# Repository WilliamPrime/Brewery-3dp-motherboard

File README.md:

# Brewery-3dp-motherboard
A 3d printer expansion board designed to help with monitoring and managing thermals in a 3d printer

# Key featurs

- supports 12-30V input
-20 buffered thermistor inputs
- 12 fan outputs each with selection between 5V,12V and Vbus
- 12V is dropped down with a buck converter on the board with 12A max
  - if the input voltage is 12V the 12V buck shouldnt be used
- 5V is dropped down with a buck converter on the board with 12A max

- 4 Pwmed outputs meant for heaters or really beefy fans
- 35A max per output, 62A max across all of the ports
  - the heaters are on a seperate fuse and terminal in, allowing you to save power budget for fans or just run things at a different voltage.

So you could you could use the thermistors to do something like 

- 12 for motors
  - would allow for checking in places where you suspect hotspots, but also coldspots.
  - would montior, Extruder, Z, and then 4 motor for an AWD gantry
- temp of outside of pannels
- ambient air temp
- electronics enclosure air temp
- lower printer air temp
- mid printer air temp
- upper printer air temp
- bed edge temp 
- frame temp

# KiCAD photos

# Firmware

This board uses an STM32F407ZGT6 MCU, which is supported by mainline klipper and marlin.

# BOM

| Part              | Item cost | shipping+tax cost | Total cost for item(s) | Notes                                 |
|-------------------|-----------|-------------------|------------------------|---------------------------------------|
| LCSC components   | $157.72   | $39.63            | $190.90                | ordering enough to populate the 5PCBs |
| JLC PCB + stencil | $92.09    | $48.06            | $140.15                | No PCBA, im handsoldering, the boards |
|                   |           |                   |                        |                                       |

Total cost $331.05

There is a detailed break down of the parts to be ordered on LCSC [**here**](https://github.com/WilliamPrime/Brewery-3dp-motherboard/blob/main/PROD/Brewery_Alpha_0.01_LCSC%20bom.csv)

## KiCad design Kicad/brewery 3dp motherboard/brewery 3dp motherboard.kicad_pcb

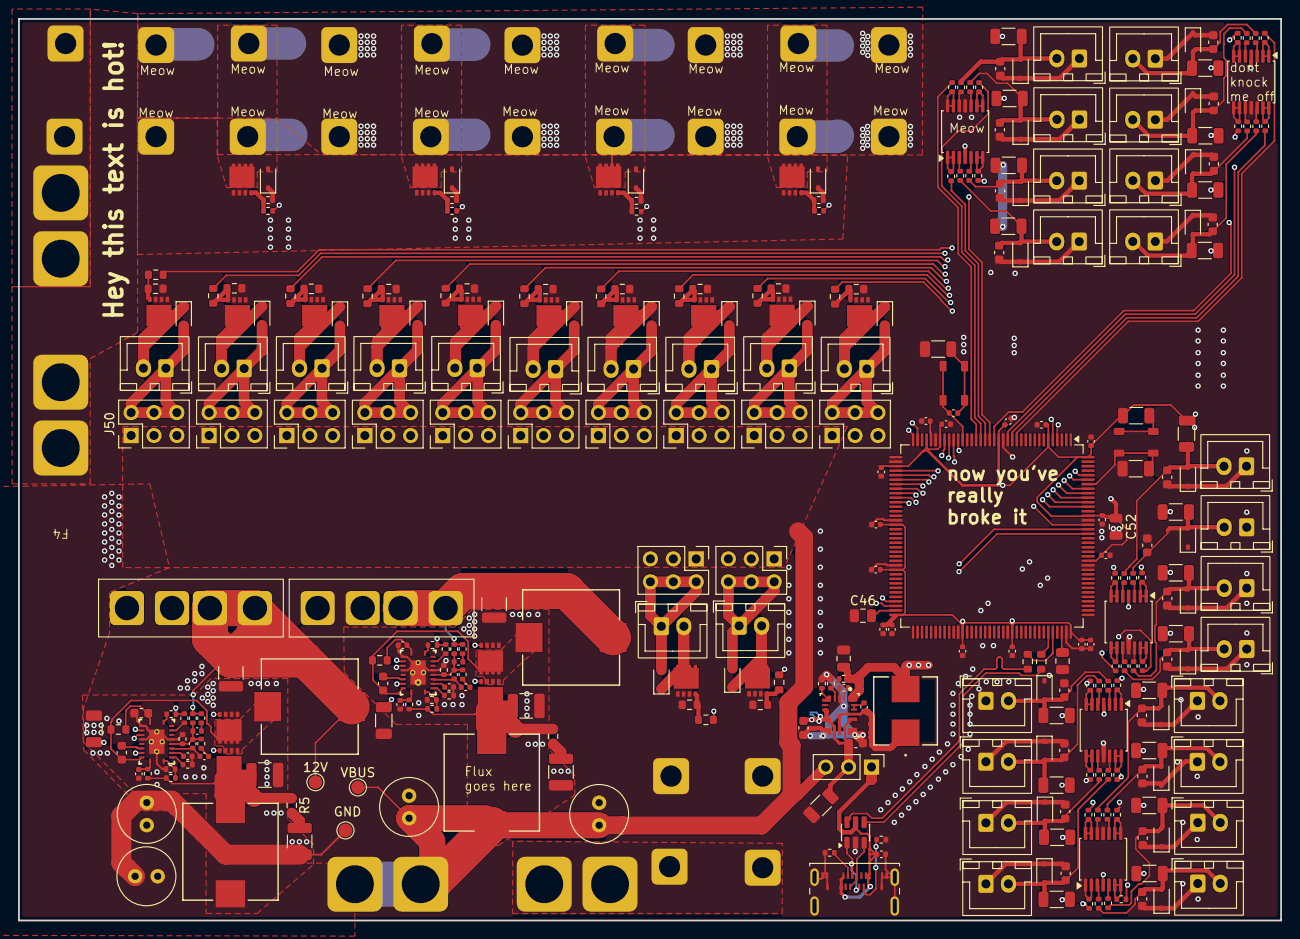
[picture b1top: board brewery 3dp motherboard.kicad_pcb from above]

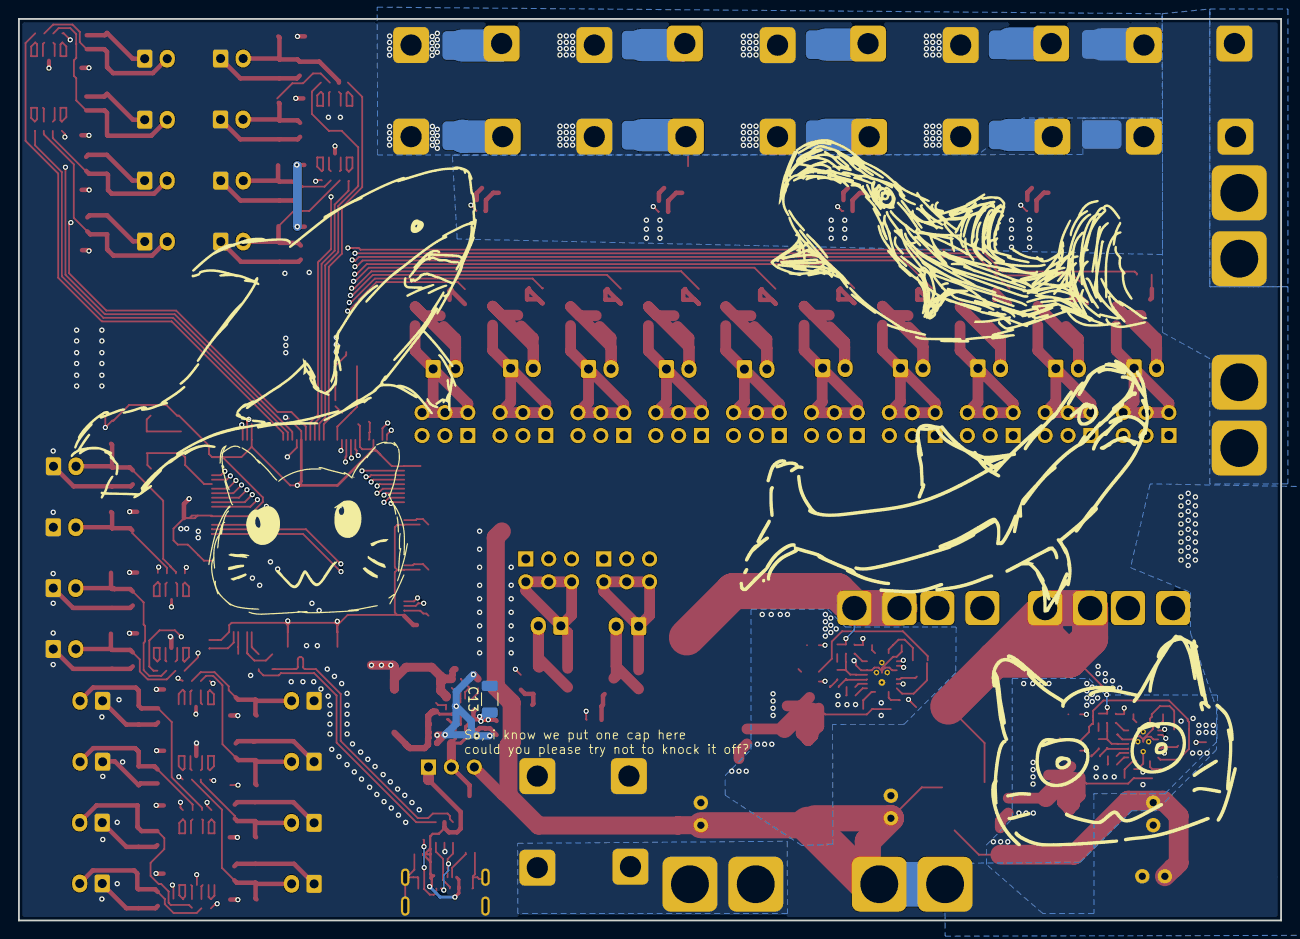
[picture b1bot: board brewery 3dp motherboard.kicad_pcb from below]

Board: 4 copper layers, 140.0 x 100.0 mm, 337 parts (6 on the bottom side), 208 nets.

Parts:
12V: TestPoint_Pad_D1.5mm
C2, C4, C22, C23: 47uF; C_Radial_D6.3mm_H7.0mm_P2.50mm
C3, C6, C7, C8, C9, C10, C72, C73, C74, C75, C76, C77, C78, C79, C80, C81, C82, C83, C84, C85, C86, C87: 4.7uF; C_0603_1608Metric
C5, C24: 10uF; C_1210_3225Metric
C11, C12: 4.7uF; C_1210_3225Metric
C13, C14: 470nF; C_1206_3216Metric
C15, C16, C26, C39, C44, C53, C54, C55, C56, C57, C58, C59, C60, C61, C66, C67, C68, C69, C70, C71: 100nF; C_0402_1005Metric
C17, C45: 1uF; C_0402_1005Metric
C18, C19: 56nF; C_0402_1005Metric
C20, C21: 2.2uF; C_1206_3216Metric
C27, C28: 100nF; C_0603_1608Metric
C29: 6.8pF; C_0603_1608Metric
C30: 6.8pF; C_0402_1005Metric
C31, C32: 8.2nF; C_0402_1005Metric
C33, C34: 1nF; C_0402_1005Metric
C35: 47uF; C_0805_2012Metric
C40, C41: 390pF; C_0402_1005Metric
C42, C43: 22uF; C_1210_3225Metric
C46, C47: 2.2uF; C_0805_2012Metric
C52: 4.7uF; C_0805_2012Metric
D1, D2, D3, D4, D21, D22, D23, D24, D25, D26, D27, D28, D29, D30, D31, D32, D33, D34, D35, D36, D37, D38, D39, D40, D41, D42, D43, D44, D45, D46, D47, D48, D49, D50, D51, D52: D55V0M1B2WS-7; D_SOD-323
F1, F4: Fuse; Untitled
F2, F3: Fuse; XF-509P
GND: TestPoint_Pad_D1.5mm
J1: power in; KF135T-10.16-2P
J2, J3, J4, J5, J29, J31, J33, J35, J37, J39, J41, J43, J45, J47, J49, J51, J52, J53, J54, J55, J56, J57, J58, J59, J60, J61, J62, J63, J64, J65, J66, J67: JST-XH; JST_XH_B2B-XH-A_1x02_P2.50mm_Vertical
J6: Conn_01x03_Pin; PinHeader_1x03_P2.54mm_Vertical
J11: USB_C_Receptacle_USB2.0_14P; USB_C_Receptacle_Amphenol_124019772112A
J16: heater in; KF135T-10.16-2P
J26, J27, J68, J69: Screw_Terminal_01x02; KF135T-10.16-2P
J28, J30, J32, J34, J36, J38, J40, J42, J44, J46, J48, J50: jumpers; PinHeader_2x03_P2.54mm_Vertical
L1, L2, L4, L5: 3.3uH; IND_SRP1038A_BRN-M
L3: 2.2uH; 7x6.6mm-inductor-M
R1, R2, R3, R4, R29, R122, R123, R128, R129, R134, R135, R140, R141, R146, R147, R152, R153, R158, R159, R164, R165: 4.7k; R_1206_3216Metric
R5, R6: 1ohm; R_0603_1608Metric
R7, R8, R9, R10, R15, R16, R17, R18, R124, R125, R126, R127, R130, R131, R132, R133, R136, R137, R138, R139, R142, R143, R144, R145, R148, R149, R150, R151, R154, R155, R156, R157, R160, R161, R162, R163, R166, R167, R168, R169: 1k; R_0402_1005Metric
R11, R13: 80.4k; R_0402_1005Metric
R12, R14: 8.45k; R_0402_1005Metric
R19, R20: 2.1ohm; R_0402_1005Metric
R21: 5.76k; R_0402_1005Metric
R22, R23, R24, R25, R26, R27: 20k; R_0402_1005Metric
R28, R30: 100; R_1206_3216Metric
R40: 51k; R_0402_1005Metric
R41: 22.1K; R_0402_1005Metric
R42, R43: 1.02k; R_0603_1608Metric
R44, R45: 1.47k; R_0402_1005Metric
R46: 1.5k; R_0402_1005Metric
R47: 3.4k; R_0402_1005Metric
R52, R53: 5.1k; R_0402_1005Metric
R54: 21k; R_0402_1005Metric
R55: 18k; R_0402_1005Metric
R60, R61: 130ohm; R_0402_1005Metric
R80, R84, R86, R88: 100; R_0402_1005Metric
R81, R85, R87, R89: 10k; R_0402_1005Metric
R82, R83: 22; R_0603_1608Metric
R90, R91, R92, R93, R94: 0Ohm; Milliohm HoT-2-4.5-11-I
R98, R100, R102, R104, R106, R108, R110, R112, R114, R116, R118, R120: 2k; R_0603_1608Metric
R99, R101, R103, R105, R107, R109, R111, R113, R115, R117, R119, R121: 20k; R_0603_1608Metric
SW1, SW2: SW_Push; CAX TS-1185-W-4P-H1.8-160
U1, U30, U31, U32, U33: MCP6004; TSSOP-14_4.4x5mm_P0.65mm
U2: LM61430AFSQRJRRQ1; RJR0014A-MFG
U4, U5: LM25145RGYR; RGY0020B
U7, U8, U9, U10, U16, U17, U18, U19, U20, U21, U22, U23, U24, U25, U26, U27, U28, U29, U34, U35: DOZ45N03T
U11: USBLC6-2SC6; SOT-23-6
U14: STM32F407Z_E-G_Tx; LQFP-144_20x20mm_P0.5mm
VBUS: TestPoint_Pad_D1.5mm

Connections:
+3.3V: C35.1, C52.1, C53.1, C54.1, C55.1, C56.1, C57.1, C58.1, C59.1, C60.1, C61.1, C66.1, C67.1, C68.1, C69.1, C70.1, C71.1, L3.2, R1.2, R2.2, R3.2, R4.2, R28.1, R40.2, R122.2, R123.2, R128.2, R129.2, R134.2, R135.2, R140.2, R141.2, R146.2, R147.2, R152.2, R153.2, R158.2, R159.2, R164.2, R165.2, U1.4 (V+), U2.1 (BIAS), U14.6 (VBAT), U14.17 (VDD), U14.30 (VDD), U14.33 (VDDA), U14.39 (VDD), U14.52 (VDD), U14.62 (VDD), U14.72 (VDD), U14.84 (VDD), U14.95 (VDD), U14.108 (VDD), U14.121 (VDD), U14.131 (VDD), U14.144 (VDD), U30.4 (V+), U31.4 (V+), U32.4 (V+), U33.4 (V+)
+5V: F3.1, J28.5, J30.5, J32.5, J34.5, J36.5, J38.5, J40.5, J42.5, J44.5, J46.5, J48.5, J50.5
+12V: F2.1, J28.3, J30.3, J32.3, J34.3, J36.3, J38.3, J40.3, J42.3, J44.3, J46.3, J48.3, J50.3
BOOT0: R29.2, SW2.2, U14.138 (BOOT0)
Fan1: R98.1, U14.127 (PG12)
Fan2: R106.1, U14.128 (PG13)
Fan3: R100.1, U14.129 (PG14)
Fan4: R108.1, U14.133 (PB3)
Fan5: R102.1, U14.134 (PB4)
Fan6: R110.1, U14.135 (PB5)
Fan7: R104.1, U14.136 (PB6)
Fan8: R112.1, U14.137 (PB7)
Fan9: R114.1, U14.139 (PB8)
Fan10: R118.1, U14.140 (PB9)
Fan11: R116.1, U14.5 (PE6)
Fan12: R120.1, U14.4 (PE5)
GND: C2.2, C3.2, C4.2, C5.2, C6.2, C7.2, C8.2, C9.2, C10.2, C11.2, C12.2, C13.2, C14.2, C15.2, C16.2, C17.2, C18.2, C19.2, C20.2, C21.2, C22.2, C23.2, C24.2, C29.2, C30.2, C35.2, C39.1, C42.2, C43.2, C45.1, C46.1, C47.1, C52.2, C53.2, C54.2, C55.2, C56.2, C57.2, C58.2, C59.2, C60.2, C61.2, C66.2, C67.2, C68.2, C69.2, C70.2, C71.2, C72.2, C73.2, C74.2, C75.2, C76.2, C77.2, C78.2, C79.2, C80.2, C81.2, C82.2, C83.2, C84.2, C85.2, C86.2, C87.2, D1.1 (A1), D2.1 (A1), D3.1 (A1), D4.1 (A1), D33.1 (A1), D34.1 (A1), D35.1 (A1), D36.1 (A1), D37.1 (A1), D38.1 (A1), D39.1 (A1), D40.1 (A1), D41.1 (A1), D42.1 (A1), D43.1 (A1), D44.1 (A1), D45.1 (A1), D46.1 (A1), D47.1 (A1), D48.1 (A1), D49.1 (A1), D50.1 (A1), D51.1 (A1), D52.1 (A1), GND.1, J1.1, J2.1, J3.1, J4.1, J5.1, J11.A1 (GND), J11.A12 (GND), J11.B1 (GND), J11.B12 (GND), J11.SH (SHIELD), J16.1, J52.1, J53.1, J54.1, J55.1, J56.1, J57.1, J58.1, J59.1, J60.1, J61.1, J62.1, J63.1, J64.1, J65.1, J66.1, J67.1, R12.1, R14.1, R21.2, R22.1, R23.1, R29.1, R30.1, R41.1, R46.1, R47.1, R52.2, R53.2, R81.1, R85.1, R87.1, R89.1, R94.1, R94.2, R99.1, R101.1, R103.1, R105.1, R107.1, R109.1, R111.1, R113.1, R115.1, R117.1, R119.1, R121.1, U1.11 (V-), U2.3 (AGND), U2.9 (PGND1), U2.11 (PGND2), U4.6 (AGND), U4.12 (PGND), U4.15 (EP), U4.21 (EP), U4.GND, U5.6 (AGND), U5.12 (PGND), U5.15 (EP), U5.21 (EP), U5.GND, U8.1 (Source), U10.1 (Source), U11.2 (GND), U14.16 (VSS), U14.31 (VSSA), U14.38 (VSS), U14.51 (VSS), U14.61 (VSS), U14.83 (VSS), U14.94 (VSS), U14.107 (VSS), U14.120 (VSS), U14.130 (VSS), U16.1 (Source), U17.1 (Source), U18.1 (Source), U19.1 (Source), U20.1 (Source), U21.1 (Source), U22.1 (Source), U23.1 (Source), U24.1 (Source), U25.1 (Source), U26.1 (Source), U27.1 (Source), U28.1 (Source), U29.1 (Source), U30.11 (V-), U31.11 (V-), U32.11 (V-), U33.11 (V-), U34.1 (Source), U35.1 (Source)
Heater1: R84.1, U14.70 (PB11)
Heater2: R86.1, U14.69 (PB10)
Heater3: R80.1, U14.36 (PA2)
Heater4: R88.1, U14.35 (PA1)
unnamed: C5.1, R6.1
unnamed: C24.1, R5.2
unnamed: C31.2, R44.2
unnamed: C32.2, R45.2
unnamed: C40.1, R60.1
unnamed: C41.1, R61.1
unnamed: 12V.1, C42.1, F2.2, L4.2, R54.2, R60.2
unnamed: C43.1, F3.2, L5.2, R55.2, R61.2
unnamed: C44.1, R30.2, SW1.1
unnamed: C6.1, D1.2 (A2), J2.2, R1.1, R7.2
unnamed: C7.1, D2.2 (A2), J3.2, R2.1, R8.2
unnamed: C8.1, D3.2 (A2), J4.2, R3.1, R9.2
unnamed: C9.1, D4.2 (A2), J5.2, R4.1, R10.2
unnamed: D21.1 (A1), J29.2, U18.3 (Drain)
unnamed: D21.2 (A2), J28.2, J28.4, J28.6, J29.1
unnamed: D22.1 (A1), J31.2, U19.3 (Drain)
unnamed: D22.2 (A2), J30.2, J30.4, J30.6, J31.1
unnamed: D23.1 (A1), J33.2, U20.3 (Drain)
unnamed: D23.2 (A2), J32.2, J32.4, J32.6, J33.1
unnamed: D24.1 (A1), J35.2, U21.3 (Drain)
unnamed: D24.2 (A2), J34.2, J34.4, J34.6, J35.1
unnamed: D25.1 (A1), J37.2, U22.3 (Drain)
unnamed: D25.2 (A2), J36.2, J36.4, J36.6, J37.1
unnamed: D26.1 (A1), J39.2, U23.3 (Drain)
unnamed: D26.2 (A2), J38.2, J38.4, J38.6, J39.1
unnamed: D27.1 (A1), J41.2, U24.3 (Drain)
unnamed: D27.2 (A2), J40.2, J40.4, J40.6, J41.1
unnamed: D28.1 (A1), J43.2, U25.3 (Drain)
unnamed: D28.2 (A2), J42.2, J42.4, J42.6, J43.1
unnamed: D29.1 (A1), J45.2, U26.3 (Drain)
unnamed: D29.2 (A2), J44.2, J44.4, J44.6, J45.1
unnamed: D30.1 (A1), J47.2, U27.3 (Drain)
unnamed: D30.2 (A2), J46.2, J46.4, J46.6, J47.1
unnamed: D31.1 (A1), J49.2, U28.3 (Drain)
unnamed: D31.2 (A2), J48.2, J48.4, J48.6, J49.1
unnamed: D32.1 (A1), J51.2, U29.3 (Drain)
unnamed: D32.2 (A2), J50.2, J50.4, J50.6, J51.1
unnamed: C72.1, D33.2 (A2), J52.2, R122.1, R124.2
unnamed: C73.1, D34.2 (A2), J53.2, R123.1, R125.2
unnamed: C74.1, D35.2 (A2), J54.2, R128.1, R130.2
unnamed: C75.1, D36.2 (A2), J55.2, R129.1, R131.2
unnamed: C76.1, D37.2 (A2), J56.2, R134.1, R136.2
unnamed: C77.1, D38.2 (A2), J57.2, R135.1, R137.2
unnamed: C78.1, D39.2 (A2), J58.2, R140.1, R142.2
unnamed: C79.1, D40.2 (A2), J59.2, R141.1, R143.2
unnamed: C80.1, D41.2 (A2), J60.2, R146.1, R148.2
unnamed: C81.1, D42.2 (A2), J61.2, R147.1, R149.2
unnamed: C82.1, D43.2 (A2), J62.2, R152.1, R154.2
unnamed: C83.1, D44.2 (A2), J63.2, R153.1, R155.2
unnamed: C84.1, D45.2 (A2), J64.2, R158.1, R160.2
unnamed: C85.1, D46.2 (A2), J65.2, R159.1, R161.2
unnamed: C86.1, D47.2 (A2), J66.2, R164.1, R166.2
unnamed: C87.1, D48.2 (A2), J67.2, R165.1, R167.2
unnamed: D49.2 (A2), J26.2, R90.1, R90.2, U16.3 (Drain)
unnamed: D50.2 (A2), J68.2, R91.1, R91.2, U34.3 (Drain)
unnamed: D51.2 (A2), J69.2, R92.1, R92.2, U35.3 (Drain)
unnamed: D52.2 (A2), J27.2, R93.1, R93.2, U17.3 (Drain)
unnamed: F1.2, J1.2
unnamed: C3.1, C10.1, C13.1, C14.1, J6.2, U2.7 (EN_SYNC), U2.8 (VIN1), U2.12 (VIN2)
unnamed: J11.A5 (CC1), R52.1
unnamed: J11.B5 (CC2), R53.1
unnamed: J11.A6 (D+), J11.B6 (D+), U11.1 (I/O1)
unnamed: J11.A7 (D-), J11.B7 (D-), U11.3 (I/O2)
unnamed: F4.2, J16.2
unnamed: R28.2, SW2.1
unnamed: R7.1, U1.3 (+)
unnamed: R15.2, U1.1, U1.2 (-)
unnamed: R8.1, U1.5 (+)
unnamed: R16.2, U1.6 (-), U1.7
unnamed: R10.1, U1.10 (+)
unnamed: R18.2, U1.8, U1.9 (-)
unnamed: R9.1, U1.12 (+)
unnamed: R17.2, U1.13 (-), U1.14
unnamed: C26.1, U2.13 (RBOOT), U2.14 (CBOOT)
unnamed: R40.1, R41.2, U2.4 (FB)
unnamed: R21.1, U2.5 (PGOOD)
unnamed: C26.2, L3.1, U2.10 (SW)
unnamed: C17.1, U2.2 (VCC)
unnamed: C27.1, U4.17 (BST)
unnamed: C31.1, C33.1, U4.4 (COMP)
unnamed: R11.1, R12.2, U4.1 (EN_UVLO)
unnamed: C33.2, C40.2, R44.1, R46.2, R54.1, U4.5 (FB)
unnamed: U4.18 (HO), U7.2 (Gate)
unnamed: C29.1, R42.2, U4.11 (ILIM)
unnamed: U4.13 (LO), U8.2 (Gate)
unnamed: R25.1, U4.10 (PGOOD)
unnamed: R22.2, U4.2 (RT)
unnamed: C18.1, U4.3 (SS_TRK)
unnamed: C27.2, L4.1, R42.1, U4.19 (SW), U7.1 (Source), U8.3 (Drain)
unnamed: R24.1, U4.8 (SYNCIN)
unnamed: C20.1, R24.2, R25.2, U4.14 (VCC)
unnamed: C15.1, R19.1, U4.20 (VIN)
unnamed: C28.1, U5.17 (BST)
unnamed: C32.1, C34.1, U5.4 (COMP)
unnamed: R13.1, R14.2, U5.1 (EN_UVLO)
unnamed: C34.2, C41.2, R45.1, R47.2, R55.1, U5.5 (FB)
unnamed: U5.18 (HO), U9.2 (Gate)
unnamed: C30.1, R43.2, U5.11 (ILIM)
unnamed: R27.1, U5.10 (PGOOD)
unnamed: R23.2, U5.2 (RT)
unnamed: C19.1, U5.3 (SS_TRK)
unnamed: R26.1, U5.8 (SYNCIN)
unnamed: C21.1, R26.2, R27.2, U5.14 (VCC)
unnamed: C16.1, R20.1, U5.20 (VIN)
unnamed: C11.1, L1.2, R5.1, R11.2, R19.2, U7.3 (Drain)
unnamed: C12.1, L2.2, R6.2, R13.2, R20.2, U9.3 (Drain)
unnamed: C28.2, L5.1, R43.1, U5.19 (SW), U9.1 (Source), U10.3 (Drain)
unnamed: U5.13 (LO), U10.2 (Gate)
unnamed: C44.2, SW1.2, U14.25 (NRST)
unnamed: R82.1, U14.103 (PA11)
unnamed: R83.1, U14.104 (PA12)
unnamed: C46.2, U14.71 (VCAP_1)
unnamed: C47.2, U14.106 (VCAP_2)
unnamed: C45.2, U14.32 (VREF+)
unnamed: R80.2, R81.2, U16.2 (Gate)
unnamed: R88.2, R89.2, U17.2 (Gate)
unnamed: R98.2, R99.2, U18.2 (Gate)
unnamed: R100.2, R101.2, U19.2 (Gate)
unnamed: R102.2, R103.2, U20.2 (Gate)
unnamed: R104.2, R105.2, U21.2 (Gate)
unnamed: R106.2, R107.2, U22.2 (Gate)
unnamed: R108.2, R109.2, U23.2 (Gate)
unnamed: R110.2, R111.2, U24.2 (Gate)
unnamed: R112.2, R113.2, U25.2 (Gate)
unnamed: R114.2, R115.2, U26.2 (Gate)
unnamed: R116.2, R117.2, U27.2 (Gate)
unnamed: R118.2, R119.2, U28.2 (Gate)
unnamed: R120.2, R121.2, U29.2 (Gate)
unnamed: R124.1, U30.3 (+)
unnamed: R126.2, U30.1, U30.2 (-)
unnamed: R125.1, U30.5 (+)
unnamed: R127.2, U30.6 (-), U30.7
unnamed: R131.1, U30.10 (+)
unnamed: R133.2, U30.8, U30.9 (-)
unnamed: R130.1, U30.12 (+)
unnamed: R132.2, U30.13 (-), U30.14
unnamed: R136.1, U31.3 (+)
unnamed: R138.2, U31.1, U31.2 (-)
unnamed: R137.1, U31.5 (+)
unnamed: R139.2, U31.6 (-), U31.7
unnamed: R143.1, U31.10 (+)
unnamed: R145.2, U31.8, U31.9 (-)
unnamed: R142.1, U31.12 (+)
unnamed: R144.2, U31.13 (-), U31.14
unnamed: R148.1, U32.3 (+)
unnamed: R150.2, U32.1, U32.2 (-)
unnamed: R149.1, U32.5 (+)
unnamed: R151.2, U32.6 (-), U32.7
unnamed: R155.1, U32.10 (+)
unnamed: R157.2, U32.8, U32.9 (-)
unnamed: R154.1, U32.12 (+)
unnamed: R156.2, U32.13 (-), U32.14
unnamed: R160.1, U33.3 (+)
unnamed: R162.2, U33.1, U33.2 (-)
unnamed: R161.1, U33.5 (+)
unnamed: R163.2, U33.6 (-), U33.7
unnamed: R167.1, U33.10 (+)
unnamed: R169.2, U33.8, U33.9 (-)
unnamed: R166.1, U33.12 (+)
unnamed: R168.2, U33.13 (-), U33.14
unnamed: R84.2, R85.2, U34.2 (Gate)
unnamed: R86.2, R87.2, U35.2 (Gate)
Thermistor1: R15.1, U14.40 (PA4)
Thermistor2: R16.1, U14.45 (PC5)
Thermistor3: R17.1, U14.41 (PA5)
Thermistor4: R18.1, U14.46 (PB0)
Thermistor5: R126.1, U14.47 (PB1)
Thermistor6: R127.1, U14.43 (PA7)
Thermistor7: R132.1, U14.44 (PC4)
Thermistor8: R133.1, U14.42 (PA6)
Thermistor9: R138.1, U14.26 (PC0)
Thermistor10: R139.1, U14.27 (PC1)
Thermistor11: R144.1, U14.28 (PC2)
Thermistor12: R145.1, U14.29 (PC3)
Thermistor13: R150.1, U14.13 (PF3)
Thermistor14: R151.1, U14.18 (PF6)
Thermistor15: R156.1, U14.14 (PF4)
Thermistor16: R157.1, U14.15 (PF5)
Thermistor17: R162.1, U14.20 (PF8)
Thermistor18: R163.1, U14.19 (PF7)
Thermistor19: R168.1, U14.22 (PF10)
Thermistor20: R169.1, U14.21 (PF9)
USB5V: C39.2, J6.1, J11.A4 (VBUS), J11.A9 (VBUS), J11.B4 (VBUS), J11.B9 (VBUS), U11.5 (VBUS)
USB_D+: R83.2, U11.6 (I/O1)
USB_D-: R82.2, U11.4 (I/O2)
VBUS: C2.1, C4.1, C22.1, C23.1, F1.1, J6.3, J28.1, J30.1, J32.1, J34.1, J36.1, J38.1, J40.1, J42.1, J44.1, J46.1, J48.1, J50.1, L1.1, L2.1, VBUS.1
VHeaters: F4.1, J26.1, J27.1, J68.1, J69.1

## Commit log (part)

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2026-06-07 Initialize README with project details
    Added project description for Brewery-3dp-motherboard.
2026-06-07 Add initial project journal for Klipper board modification
    Document initial project setup and requirements for modifying a Klipper board, including MCU selection and thermistor input specifications.
2026-06-08 Corrected myself
2026-06-11 Update journal with fan circuit design progress
    Documented progress on fan circuit design, including overcurrent protection decisions, MOSFET selection, and thermistor integration. Updated task list and overall schematic.
2026-06-17 did some stuff
2026-06-20 did stuff
2026-06-22 did more stuff
2026-06-22 did stuff (uploading kicad bits)
2026-06-25 Update journal with BOM component selection details
    Documented the process of selecting components for the BOM, including considerations for voltage ratings and component availability.
2026-06-25 Enhance README with features and specifications
    Added detailed features and specifications for the 3D printer expansion board, including thermistor and fan outputs, power management, and temperature monitoring capabilities.
2026-06-25 cleaned up structure a bit
2026-06-29 Add BOM section with cost breakdown in README
    Added a Bill of Materials (BOM) section with cost details.
